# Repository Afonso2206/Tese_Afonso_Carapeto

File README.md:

This repository contains the source code, schematic, and PCB layout for the electronic badge developed as part of the thesis project of Afonso Carapeto. 

Getting Started: Reprogramming the E-Badge:

- Install the Arduino IDE: If you haven't already, download and install the Arduino IDE, which is available at https://www.arduino.cc/en/software.

Add Raspberry Pi Pico Support: In the Arduino IDE, you’ll need to add support for the Raspberry Pi Pico board (the microcontroller used in this badge). Follow these steps:
- Open the Arduino IDE and go to File > Preferences.
- In the "Additional Boards Manager URLs" field, add the following URL: https://github.com/earlephilhower/arduino-pico/releases/download/global/package_rp2040_index.json

Install the Raspberry Pi Pico Package:

- Go to Tools > Board > Boards Manager.
- Search for "Raspberry Pi Pico" in the Boards Manager.
- Install the package named Raspberry Pi Pico/RP2040 by Earle Philhower.

Select the Board and Port:

- Connect your badge (Raspberry Pi Pico) to your computer via USB.
- In the Arduino IDE, go to Tools > Board and select Raspberry Pi Pico.
- Then, under Tools > Port, select the port that corresponds to your badge.

  Upload Code to the Badge: Now you can open any of the .ino files in this repository, modify the code if desired, and click Upload to program the badge.

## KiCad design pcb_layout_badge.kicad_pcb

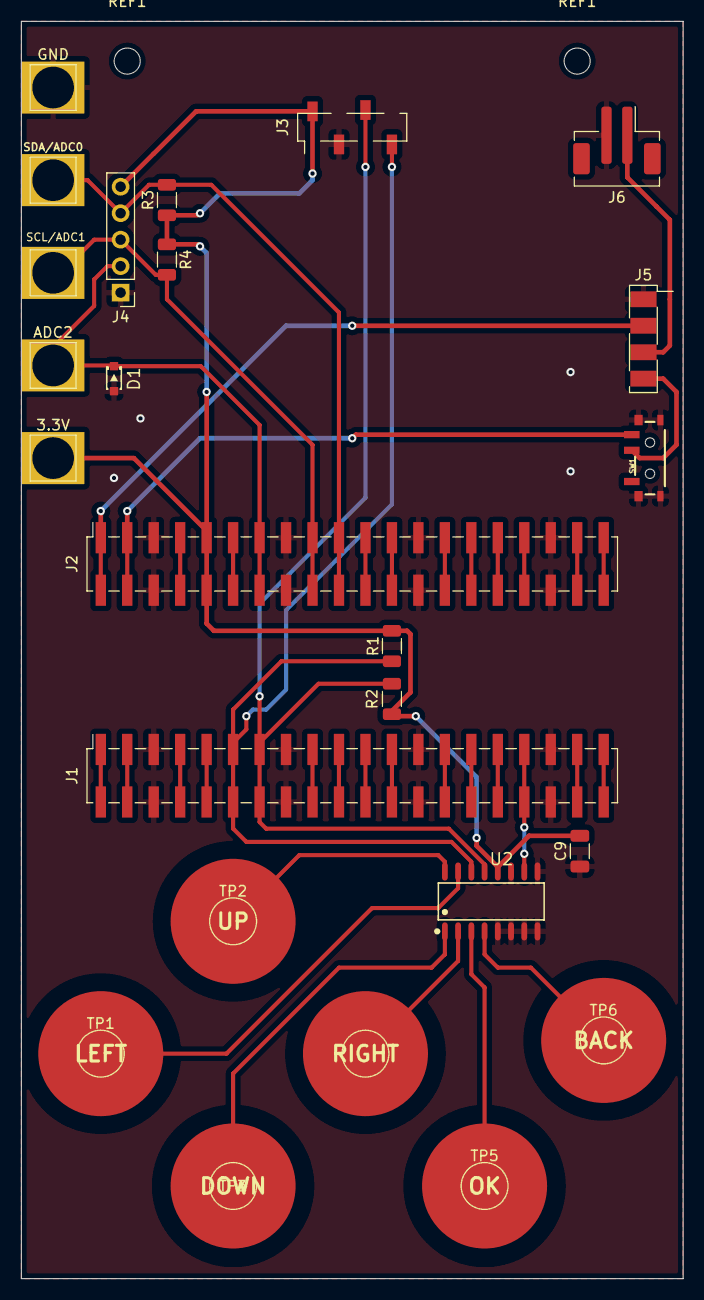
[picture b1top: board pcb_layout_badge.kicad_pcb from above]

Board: 2 copper layers, 63.5 x 120.7 mm, 28 parts (1 on the bottom side), 41 nets.

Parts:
3.3V: TestPoint; TestPoint_THTPad_4.0x4.0mm_Drill2.0mm
ADC2: TestPoint; TestPoint_THTPad_4.0x4.0mm_Drill2.0mm
C9: 0.1u; C_1206_3216Metric
D1: D_Zener; zener
G1: LOGO
GND: TestPoint; TestPoint_THTPad_4.0x4.0mm_Drill2.0mm
J1, J2: Conn_01x40_Female; PinSocket_2x20_P2.54mm_Vertical_SMD
J3: Conn_01x04_Female; PinSocket_1x04_P2.54mm_Vertical_SMD_Pin1Left
J4: Conn_01x05_Male; PinHeader_1x05_P2.54mm_Vertical
J5: Conn_01x04_Male; carregador_v2
J6: Conn_01x02_Male; JST_PH_B2B-PH-SM4-TB_1x02-1MP_P2.00mm_Vertical
R1, R2, R3, R4: 4.7k; R_1206_3216Metric
REF1, REF1#2: MountingHole_2.5mm
SCL/ADC1: TestPoint; TestPoint_THTPad_4.0x4.0mm_Drill2.0mm
SDA/ADC0: TestPoint; TestPoint_THTPad_4.0x4.0mm_Drill2.0mm
SW1: SW_SPST; SWITCH_SPST_SMD_A
TP1, TP2, TP3, TP4, TP5, TP6: TestPoint; TestPoint_Pad_D4.0mm
U2: cap_sensor; SOP-16_L10.0-W3.9-P1.27-LS6.0-BL

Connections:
+3.3V: 3.3V.1, C9.2, J2.9, J2.10, J3.1, J4.5, R1.2, R2.2, R3.1, R4.1, U2.12 (VDD)
ADC0/SDA1: J2.19, J2.20, J4.4, R3.2, SDA/ADC0.1
ADC1/SCL1: J2.17, J2.18, J4.3, R4.2, SCL/ADC1.1
ADC2: ADC2.1, D1.1 (K), J2.13, J2.14, J4.2
GND: C9.1, D1.2 (A), GND.1, J1.5, J1.6, J1.15, J1.16, J1.25, J1.26, J1.35, J1.36, J2.5, J2.6, J2.15, J2.16, J2.25, J2.26, J2.35, J2.36, J3.2, J4.1, J5.1, J6.2, SW1.GND1, SW1.GND2, SW1.GND3, SW1.GND4, U2.5 (Key7), U2.6 (Key8), U2.7 (Key9), U2.8 (Key10), U2.9 (Key11), U2.11 (VSS)
unnamed: J1.1, J1.2
unnamed: J1.3, J1.4
unnamed: J1.7, J1.8
unnamed: J1.9, J1.10
unnamed: J1.17, J1.18
unnamed: J1.19, J1.20
unnamed: J1.21, J1.22
unnamed: J1.23, J1.24
unnamed: J1.27, J1.28
unnamed: J1.29, J1.30
unnamed: J1.31, J1.32
unnamed: J1.33, J1.34, U2.10 (Key12/IRQ)
unnamed: J1.37, J1.38
unnamed: J1.39, J1.40
unnamed: J2.7, J2.8
unnamed: J2.11, J2.12
unnamed: J2.21, J2.22
unnamed: J2.23, J2.24
unnamed: J2.27, J2.28
unnamed: J2.29, J2.30
unnamed: J2.31, J2.32
unnamed: J2.33, J2.34
unnamed: J2.37, J2.38
unnamed: J2.39, J2.40
unnamed: J5.4, SW1.2 (B)
unnamed: TP1.1, U2.15 (KEY1)
unnamed: TP2.1, U2.16 (KEY2)
unnamed: TP3.1, U2.1 (KEY3)
unnamed: TP4.1, U2.2 (Key4)
unnamed: TP5.1, U2.3 (Key5)
unnamed: TP6.1, U2.4 (Key6)
SCL0: J1.13, J1.14, J3.3, R2.1, U2.13 (SCL)
SDA0: J1.11, J1.12, J3.4, R1.1, U2.14 (SDA)
VBAT: J5.3, J6.1
VBUS: J2.1, J2.2, J5.2
VSYS: J2.3, J2.4, SW1.1 (A)

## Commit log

2023-10-25 teste
2023-10-25 2o teste
2023-10-25 isdaa
2023-11-02 teste3
2023-11-03 teste4
2024-07-02 Add files via upload
    ultima versao do código, com tudo junto
